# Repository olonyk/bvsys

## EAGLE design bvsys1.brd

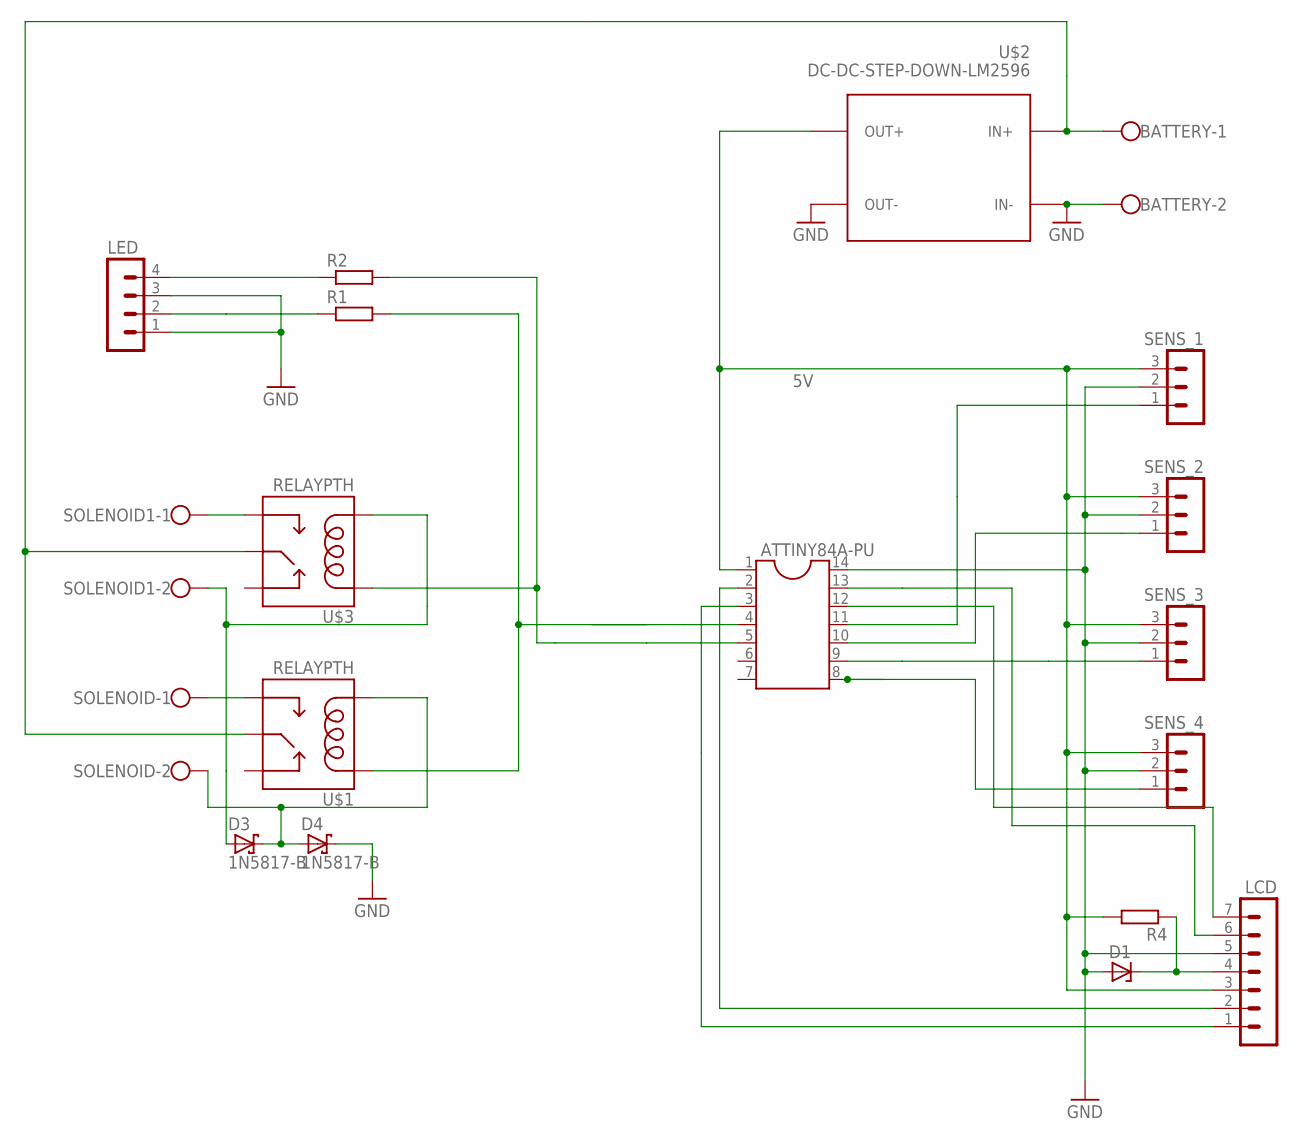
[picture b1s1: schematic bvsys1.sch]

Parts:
ATTINY84A-PU: DIL14S; SOCKET-14
BATTERY: W237-102
D1: ZENER-DIODEDO34-7; DO34Z7
D3, D4: 1N5817-B; DO41-7.6
LCD: MA07-1
LED: MA04-1
R1, R2, R4: R0204/7; 0204/7
SENS_1, SENS_2, SENS_3, SENS_4: MA03-1
SOLENOID, SOLENOID1: W237-102
U$1, U$3: RELAYPTH; SRD-05VDC-SL-C
U$2: DC-DC-STEP-DOWN-LM2596

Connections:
5V: ATTINY84A-PU.1, LCD.3, R4.2, SENS_1.3, SENS_2.3, SENS_3.3, SENS_4.3, U$2.OUT+
GND: ATTINY84A-PU.14, BATTERY.2, D1.A, D4.C, LCD.5, LED.1, LED.3, SENS_1.2, SENS_2.2, SENS_3.2, SENS_4.2, U$2.IN-, U$2.OUT-
unnamed: BATTERY.1, U$1.SWCOMMON, U$2.IN+, U$3.SWCOMMON
unnamed: ATTINY84A-PU.8, SENS_4.1
unnamed: ATTINY84A-PU.13, LCD.6
unnamed: ATTINY84A-PU.4, R1.2, U$1.COIL1
unnamed: LED.2, R1.1
unnamed: ATTINY84A-PU.12, LCD.7
unnamed: ATTINY84A-PU.9, SENS_3.1
unnamed: SOLENOID.1, U$1.SWOPEN
unnamed: ATTINY84A-PU.3, LCD.1
unnamed: ATTINY84A-PU.2, LCD.2
unnamed: LED.4, R2.1
unnamed: SOLENOID1.1, U$3.SWOPEN
unnamed: ATTINY84A-PU.10, SENS_2.1
unnamed: ATTINY84A-PU.11, SENS_1.1
unnamed: ATTINY84A-PU.5, R2.2, U$3.COIL1
unnamed: D3.A, SOLENOID1.2, U$3.COIL0
unnamed: D3.C, D4.A, SOLENOID.2, U$1.COIL0
unnamed: D1.C, LCD.4, R4.1

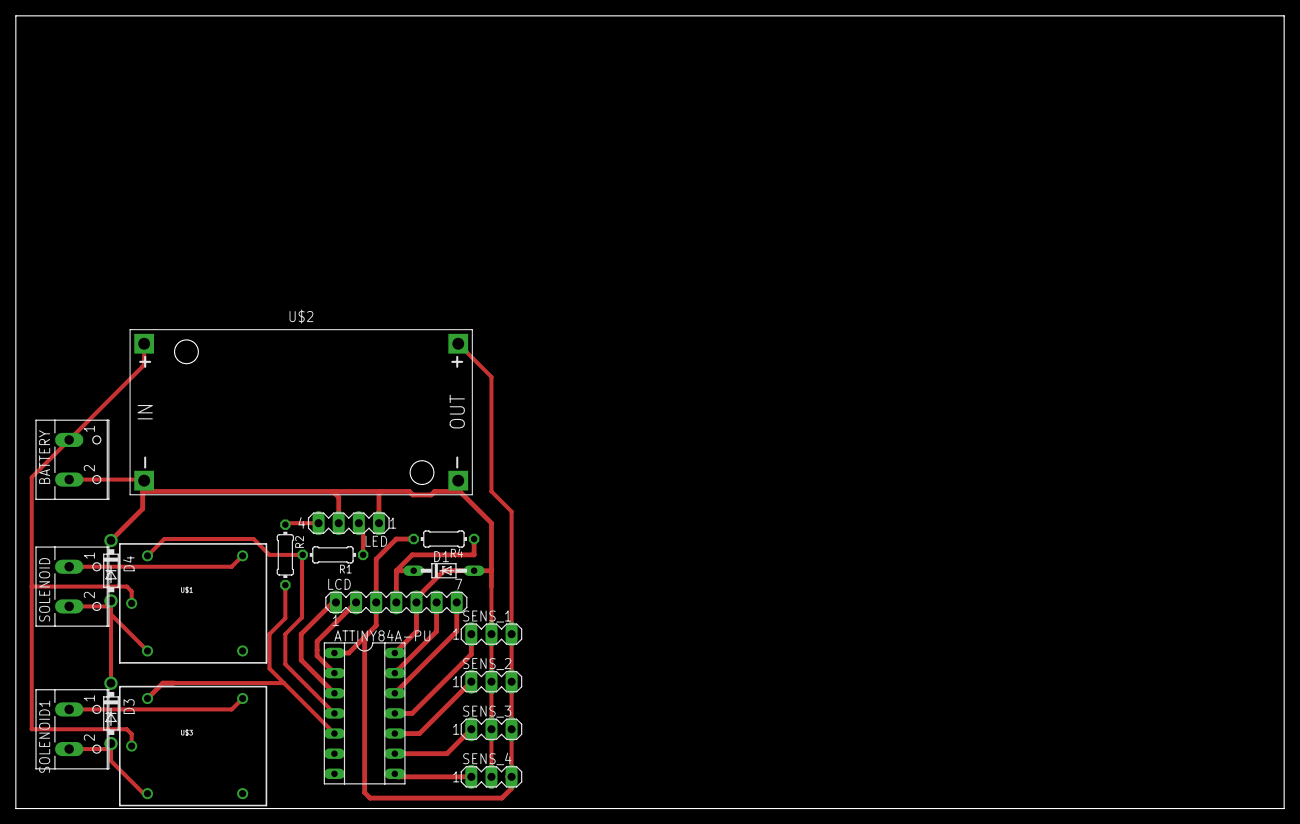
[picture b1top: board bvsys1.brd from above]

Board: 2 copper layers, 160.0 x 100.0 mm, 19 parts (0 on the bottom side), 20 nets.

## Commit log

2018-08-03 Small changes at the office

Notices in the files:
parts and their libraries:
diy-modules: Released under the Creative Commons Attribution 4.0 International License: http://creativecommons.org/licenses/by/4.0
